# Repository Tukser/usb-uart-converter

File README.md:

# usb-uart-converter
## Преобразователь на микросхеме CH340G

Принципиальная электрическая схема

Трассировка печатной платы

3D модель печатной платы

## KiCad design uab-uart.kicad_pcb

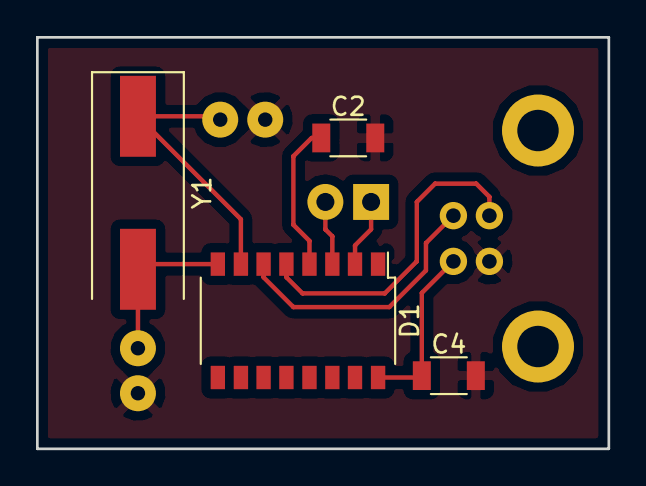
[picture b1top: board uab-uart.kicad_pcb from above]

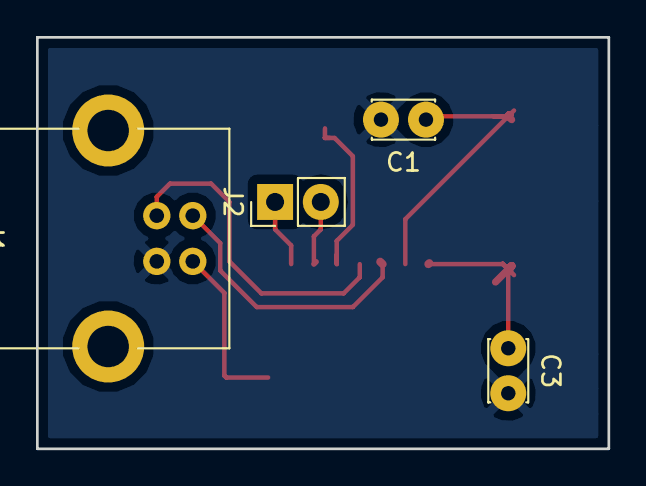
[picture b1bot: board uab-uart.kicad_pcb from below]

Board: 2 copper layers, 31.8 x 22.9 mm, 8 parts (4 on the bottom side), 9 nets.

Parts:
C1, C3: 22p; C_Disc_D3.4mm_W2.1mm_P2.50mm
C2: 10n; C_1206
C4: 10uF; C_1206
D1: CH340G; SOP-16_4.4x10.4mm_Pitch1.27mm
J1: USB_B
J2: Conn_01x02; Pin_Header_Straight_1x02_Pitch2.54mm
Y1: Crystal; Crystal_SMD_HC49-SD

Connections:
+5V: C4.1, D1.16, J1.1
GND: C1.2, C2.2, C3.2, C4.2, D1.1, J1.4
unnamed: C1.1, D1.7, Y1.1
unnamed: C2.1, D1.4
unnamed: C3.1, D1.8, Y1.2
unnamed: D1.2, J2.1
unnamed: D1.3, J2.2
unnamed: D1.5, J1.3
unnamed: D1.6, J1.2
